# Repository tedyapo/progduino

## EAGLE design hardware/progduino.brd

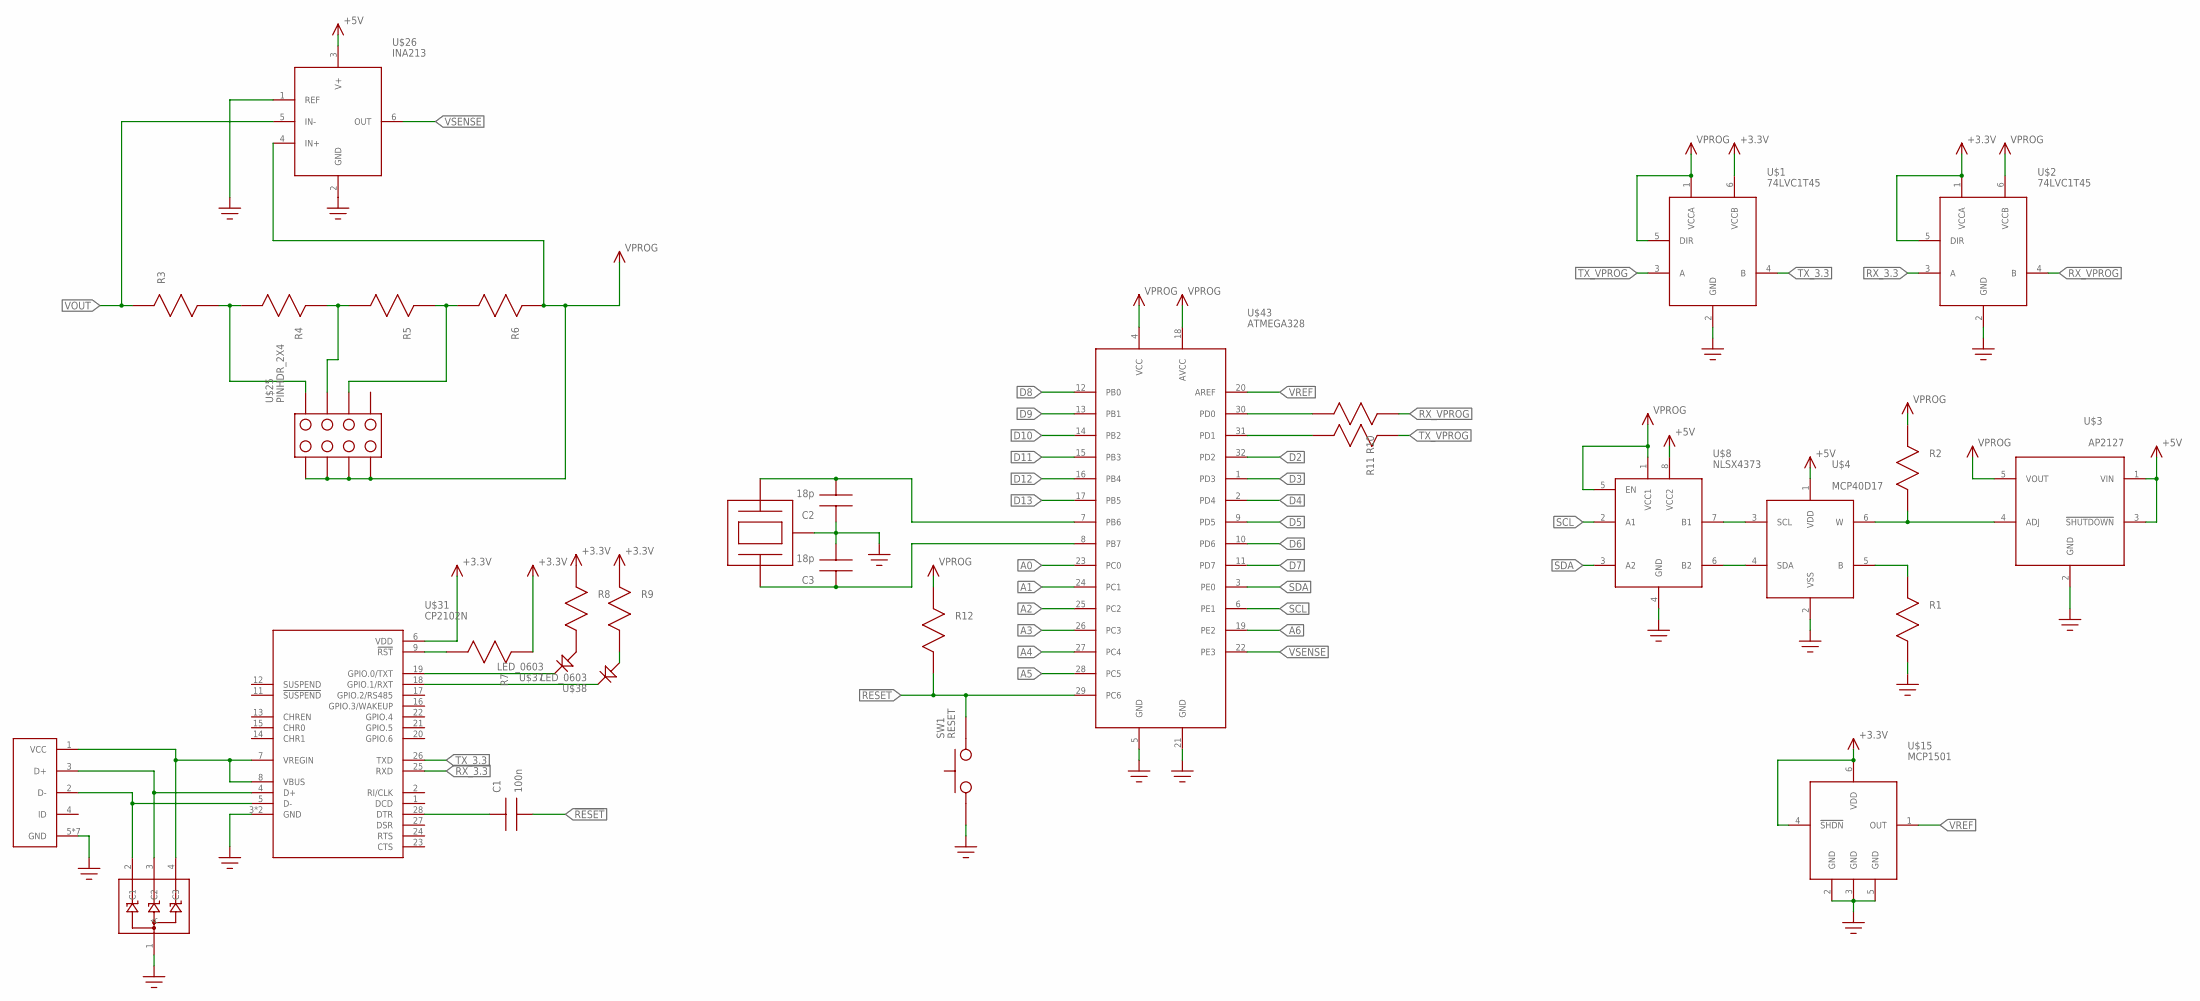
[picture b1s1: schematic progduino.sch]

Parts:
C1: 100n; C0603
C2, C3: 18p; C0603
R1, R2, R7, R8, R9, R10, R11, R12: R0603
R3, R4, R5, R6: R0805
SW1: RESET; SMD_SWITCH
U$1, U$2: 74LVC1T45; SOT23-6
U$3: AP2127; SOT23-5
U$4: MCP40D17; SC70-6
U$8: NLSX4373; SOIC8
U$15: MCP1501; SOT23-6
U$25: PINHDR_2X4
U$26: INA213; SC70-6
U$31: CP2102N; QFN28
U$37, U$38: LED_0603
U$39: USB_JACK; FCI_MICRO_USB
U$40: SP0503_TVS; SOT143
U$43: ATMEGA328; TQFP32_7X7
U$49: XTAL; CRYSTAL_3.2X2.5

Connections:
!RESET!: C1.P$2, R12.P$2, SW1.P$3, SW1.P$4, U$43.29 (PC6)
+3.3V: R7.P$1, R8.P$1, R9.P$1, U$1.6 (VCCB), U$2.1 (VCCA), U$2.5 (DIR), U$15.4 (!SHDN!), U$15.6 (VDD), U$31.6 (VDD)
+5V: U$3.1 (VIN), U$3.3 (!SHUTDOWN!), U$4.1 (VDD), U$8.8 (VCC2), U$26.3 (V+)
A0: U$43.23 (PC0)
A1: U$43.24 (PC1)
A2: U$43.25 (PC2)
A3: U$43.26 (PC3)
A4: U$43.27 (PC4)
A5: U$43.28 (PC5)
A6: U$43.19 (PE2)
D2: U$43.32 (PD2)
D3: U$43.1 (PD3)
D4: U$43.2 (PD4)
D5: U$43.9 (PD5)
D6: U$43.10 (PD6)
D7: U$43.11 (PD7)
D8: U$43.12 (PB0)
D9: U$43.13 (PB1)
D10: U$43.14 (PB2)
D11: U$43.15 (PB3)
D12: U$43.16 (PB4)
D13: U$43.17 (PB5)
GND: C2.P$1, C3.P$2, R1.P$2, SW1.P$1, SW1.P$2, U$1.2 (GND), U$2.2 (GND), U$3.2 (GND), U$4.2 (VSS), U$8.4 (GND), U$15.2 (GND), U$15.3 (GND), U$15.5 (GND), U$26.1 (REF), U$26.2 (GND), U$31.3 (GND), U$31.PAD (GND), U$39.5 (GND), U$39.GND1 (GND), U$39.GND2 (GND), U$39.GND3 (GND), U$39.GND4 (GND), U$39.GND5 (GND), U$39.GND6 (GND), U$40.1 (A), U$43.5 (GND), U$43.21 (GND), U$49.P$2 (P$CASE), U$49.P$4 (P$CASE)
unnamed: R2.P$2, U$3.4 (ADJ), U$4.6 (W)
unnamed: R1.P$1, U$4.5 (B)
unnamed: U$4.3 (SCL), U$8.7 (B1)
unnamed: U$4.4 (SDA), U$8.6 (B2)
unnamed: R3.P$2, R4.P$2, U$25.8
unnamed: R4.P$1, R5.P$2, U$25.7
unnamed: R5.P$1, R6.P$2, U$25.6
unnamed: R7.P$2, U$31.9 (!RST!)
unnamed: U$31.7 (VREGIN), U$31.8 (VBUS), U$39.1 (VCC), U$40.4 (C3)
unnamed: R8.P$2, U$37.A
unnamed: R9.P$2, U$38.A
unnamed: U$31.19 (GPIO.0/TXT), U$37.C
unnamed: U$31.18 (GPIO.1/RXT), U$38.C
unnamed: U$31.5 (D-), U$39.2 (D-), U$40.2 (C1)
unnamed: U$31.4 (D+), U$39.3 (D+), U$40.3 (C2)
unnamed: C1.P$1, U$31.28 (DTR)
unnamed: R10.P$2, U$43.30 (PD0)
unnamed: R11.P$2, U$43.31 (PD1)
unnamed: C3.P$1, U$43.8 (PB7), U$49.P$3 (P$X2)
unnamed: C2.P$2, U$43.7 (PB6), U$49.P$1 (P$X1)
RX_3.3: U$2.3 (A), U$31.25 (RXD)
RX_VPROG: R10.P$1, U$2.4 (B)
SCL: U$8.2 (A1), U$43.6 (PE1)
SDA: U$8.3 (A2), U$43.3 (PE0)
TX_3.3: U$1.4 (B), U$31.26 (TXD)
TX_VPROG: R11.P$1, U$1.3 (A)
VOUT: R3.P$1, U$26.5 (IN-)
VPROG: R2.P$1, R6.P$1, R12.P$1, U$1.1 (VCCA), U$1.5 (DIR), U$2.6 (VCCB), U$3.5 (VOUT), U$8.1 (VCC1), U$8.5 (EN), U$25.1, U$25.2, U$25.3, U$25.4, U$26.4 (IN+), U$43.4 (VCC), U$43.18 (AVCC)
VREF: U$15.1 (OUT), U$43.20 (AREF)
VSENSE: U$26.6 (OUT), U$43.22 (PE3)

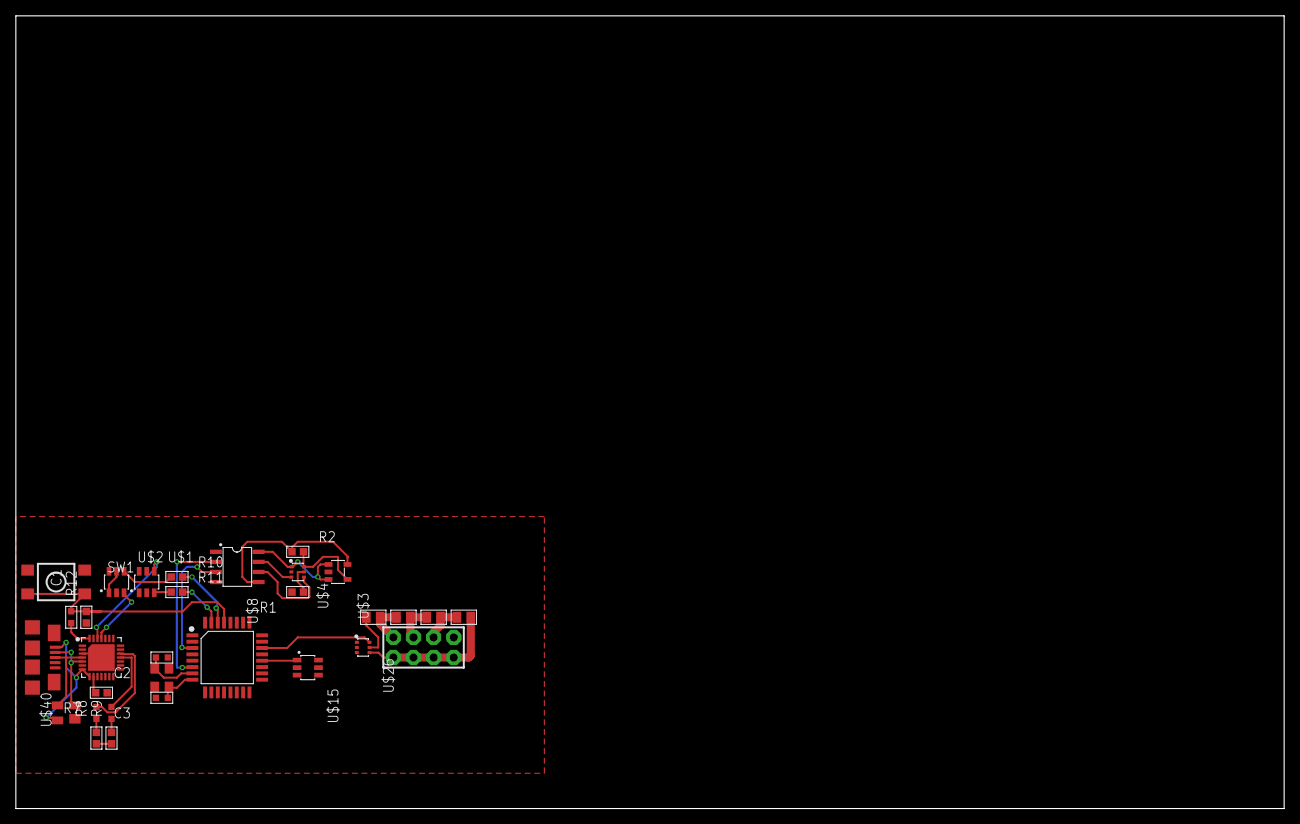
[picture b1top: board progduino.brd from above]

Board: 2 copper layers, 160.0 x 100.0 mm, 31 parts (0 on the bottom side), 34 nets.

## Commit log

2018-02-21 random checkin
